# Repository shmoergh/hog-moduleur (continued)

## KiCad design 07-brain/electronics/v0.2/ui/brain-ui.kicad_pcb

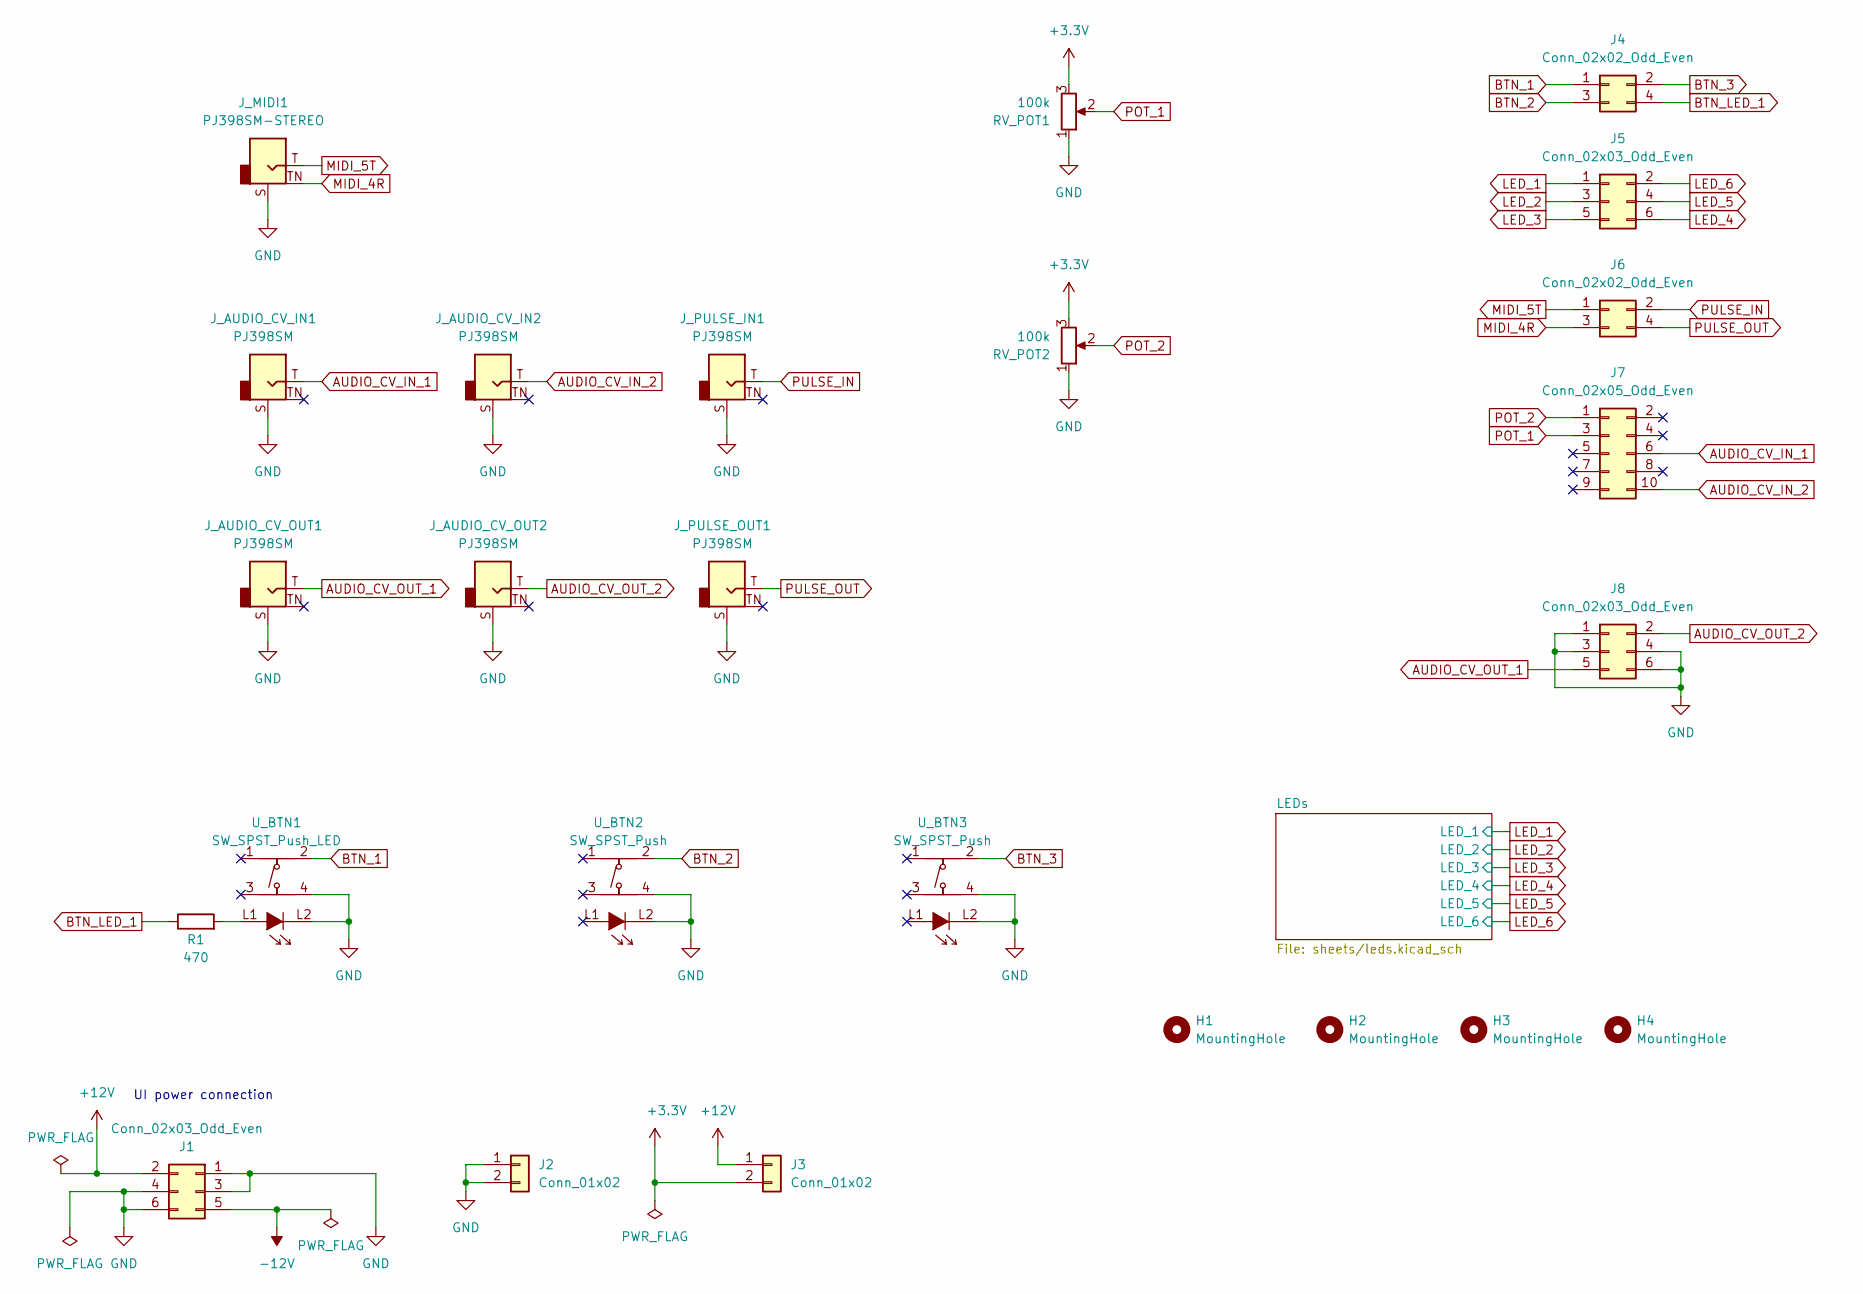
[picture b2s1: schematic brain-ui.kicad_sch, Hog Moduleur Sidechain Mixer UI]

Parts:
H1, H2, H3, H4: MountingHole; MountingHole_3.2mm_M3_DIN965_Pad
J1: Conn_02x03_Odd_Even; PinSocket_2x03_P2.54mm_Vertical; Part no. 200-SSW10301TD
J2: Conn_01x02; PinSocket_1x02_P2.54mm_Vertical; Part no. 200-SSW10201TS
J3: Conn_01x02; PinSocket_1x02_P2.54mm_Vertical
J4, J6: Conn_02x02_Odd_Even; PinSocket_2x02_P2.54mm_Vertical
J5, J8: Conn_02x03_Odd_Even; PinSocket_2x03_P2.54mm_Vertical
J7: Conn_02x05_Odd_Even; PinSocket_2x05_P2.54mm_Vertical
J_AUDIO_CV_IN1, J_AUDIO_CV_IN2: PJ398SM; Jack_3.5mm_QingPu_WQP-PJ398SM_Vertical_CircularHoles; Part no. PJ398SM
J_AUDIO_CV_OUT1, J_AUDIO_CV_OUT2: PJ398SM; Jack_3.5mm_QingPu_WQP-PJ398SM_Vertical_CircularHoles; Part no. PJ398SM
J_MIDI1: PJ398SM-STEREO; Jack_3.5mm_QingPu_WQP-PJ398SM_Vertical_CircularHoles; Part no. PJ398SM
J_PULSE_IN1: PJ398SM; Jack_3.5mm_QingPu_WQP-PJ398SM_Vertical_CircularHoles; Part no. PJ398SM
J_PULSE_OUT1: PJ398SM; Jack_3.5mm_QingPu_WQP-PJ398SM_Vertical_CircularHoles; Part no. PJ398SM
R1: 470; R_Axial_DIN0207_L6.3mm_D2.5mm_P7.62mm_Horizontal
RV_POT1, RV_POT2: 100k; Potentiometer_Bourns_Single-PTV09A; Part no. 652-PTV09A4025FB104
U_BTN1: SW_SPST_Push_LED; SPST_Circular_Pushbutton_LED
U_BTN2, U_BTN3: SW_SPST_Push; SPST_Circular_Pushbutton_LED

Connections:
+3.3V: J3.2, RV_POT1.3, RV_POT2.3
+12V: J1.2, J3.1; also elsewhere on the board
-12V: J1.5
AUDIO_CV_IN_1: J7.6, J_AUDIO_CV_IN1.T
AUDIO_CV_IN_2: J7.10, J_AUDIO_CV_IN2.T
AUDIO_CV_OUT_1: J8.5, J_AUDIO_CV_OUT1.T
AUDIO_CV_OUT_2: J8.2, J_AUDIO_CV_OUT2.T
BTN_1: J4.1, U_BTN1.2
BTN_2: J4.3, U_BTN2.2
BTN_3: J4.2, U_BTN3.2
BTN_LED_1: J4.4, R1.1
GND: J1.1, J1.3, J1.4, J1.6, J2.1, J2.2, J8.1, J8.3, J8.4, J8.6, J_AUDIO_CV_IN1.S, J_AUDIO_CV_IN2.S, J_AUDIO_CV_OUT1.S, J_AUDIO_CV_OUT2.S, J_MIDI1.S, J_PULSE_IN1.S, J_PULSE_OUT1.S, RV_POT1.1, RV_POT2.1, U_BTN1.4, U_BTN1.L2, U_BTN2.4, U_BTN2.L2, U_BTN3.4, U_BTN3.L2; also elsewhere on the board
LED_1: J5.1; also elsewhere on the board
LED_2: J5.3; also elsewhere on the board
LED_3: J5.5; also elsewhere on the board
LED_4: J5.6; also elsewhere on the board
LED_5: J5.4; also elsewhere on the board
LED_6: J5.2; also elsewhere on the board
MIDI_4R: J6.3, J_MIDI1.TN
MIDI_5T: J6.1, J_MIDI1.T
unnamed: R1.2, U_BTN1.L1
POT_1: J7.3, RV_POT1.2
POT_2: J7.1, RV_POT2.2
PULSE_IN: J6.2, J_PULSE_IN1.T
PULSE_OUT: J6.4, J_PULSE_OUT1.T

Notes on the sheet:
UI power connection

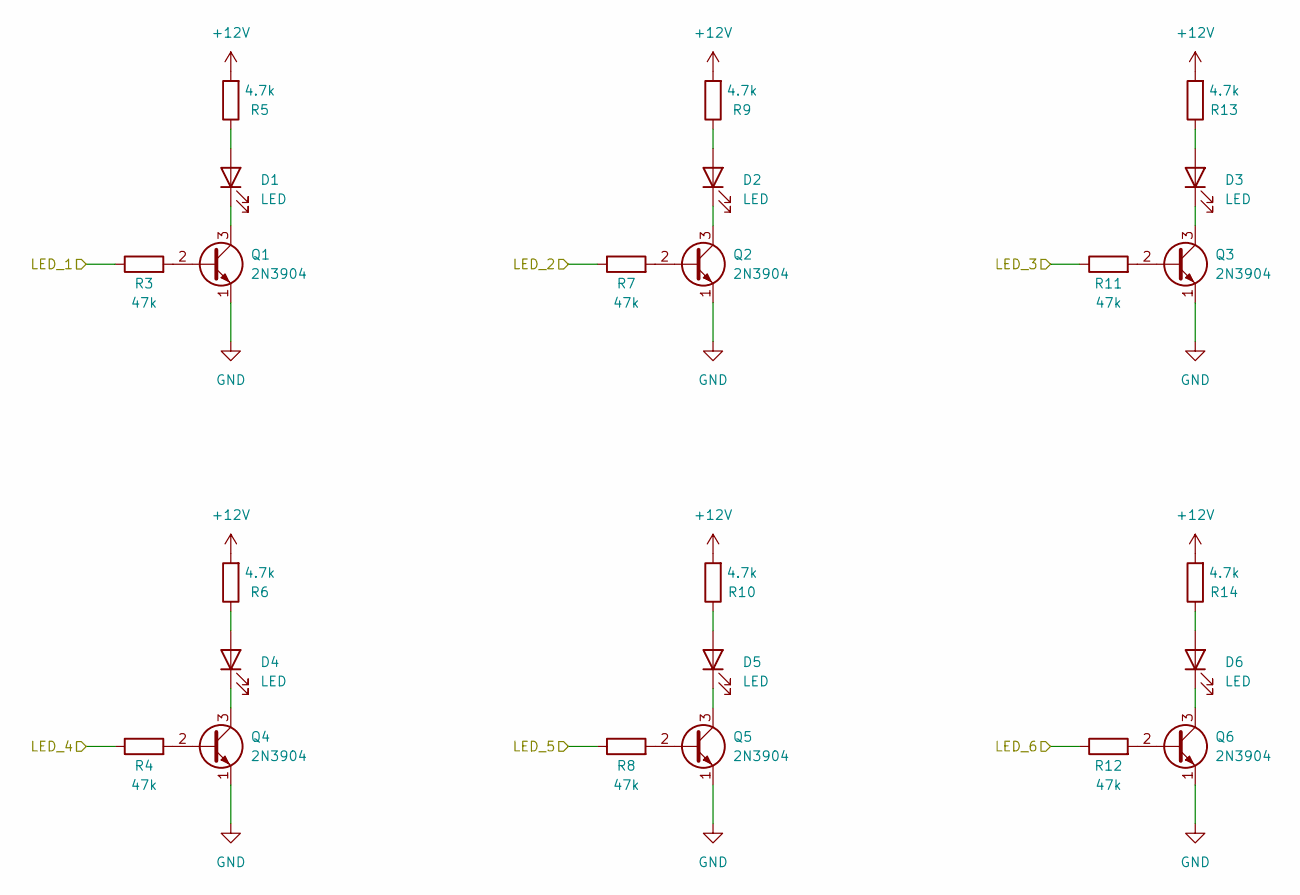
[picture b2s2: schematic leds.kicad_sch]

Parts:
D1, D2, D3, D4, D5, D6: LED; LED_D3.0mm
Q1, Q2, Q3, Q4, Q5, Q6: 2N3904; TO-92_Inline_Wide
R3, R4, R7, R8, R11, R12: 47k; R_Axial_DIN0207_L6.3mm_D2.5mm_P7.62mm_Horizontal; LCSC C25803
R5, R6, R9, R10, R13, R14: 4.7k; R_Axial_DIN0207_L6.3mm_D2.5mm_P7.62mm_Horizontal

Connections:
+12V: R5.2, R6.2, R9.2, R10.2, R13.2, R14.2; also elsewhere on the board
GND: Q1.1 (E), Q2.1 (E), Q3.1 (E), Q4.1 (E), Q5.1 (E), Q6.1 (E); also elsewhere on the board
LED_1: R3.1; also elsewhere on the board
LED_2: R7.1; also elsewhere on the board
LED_3: R11.1; also elsewhere on the board
LED_4: R4.1; also elsewhere on the board
LED_5: R8.1; also elsewhere on the board
LED_6: R12.1; also elsewhere on the board
unnamed: D1.2 (A), R5.1
unnamed: D1.1 (K), Q1.3 (C)
unnamed: D2.2 (A), R9.1
unnamed: D2.1 (K), Q2.3 (C)
unnamed: D3.2 (A), R13.1
unnamed: D3.1 (K), Q3.3 (C)
unnamed: D4.2 (A), R6.1
unnamed: D4.1 (K), Q4.3 (C)
unnamed: D5.2 (A), R10.1
unnamed: D5.1 (K), Q5.3 (C)
unnamed: D6.2 (A), R14.1
unnamed: D6.1 (K), Q6.3 (C)
unnamed: Q1.2 (B), R3.2
unnamed: Q2.2 (B), R7.2
unnamed: Q3.2 (B), R11.2
unnamed: Q4.2 (B), R4.2
unnamed: Q5.2 (B), R8.2
unnamed: Q6.2 (B), R12.2

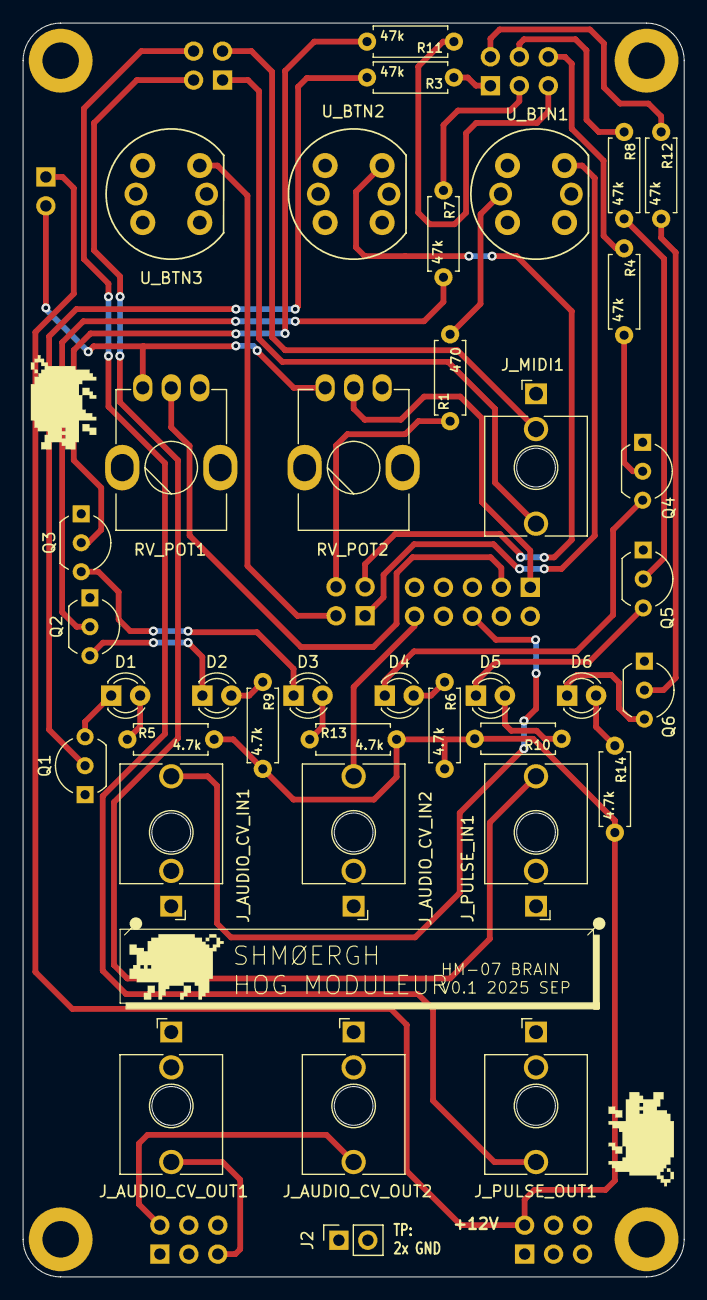
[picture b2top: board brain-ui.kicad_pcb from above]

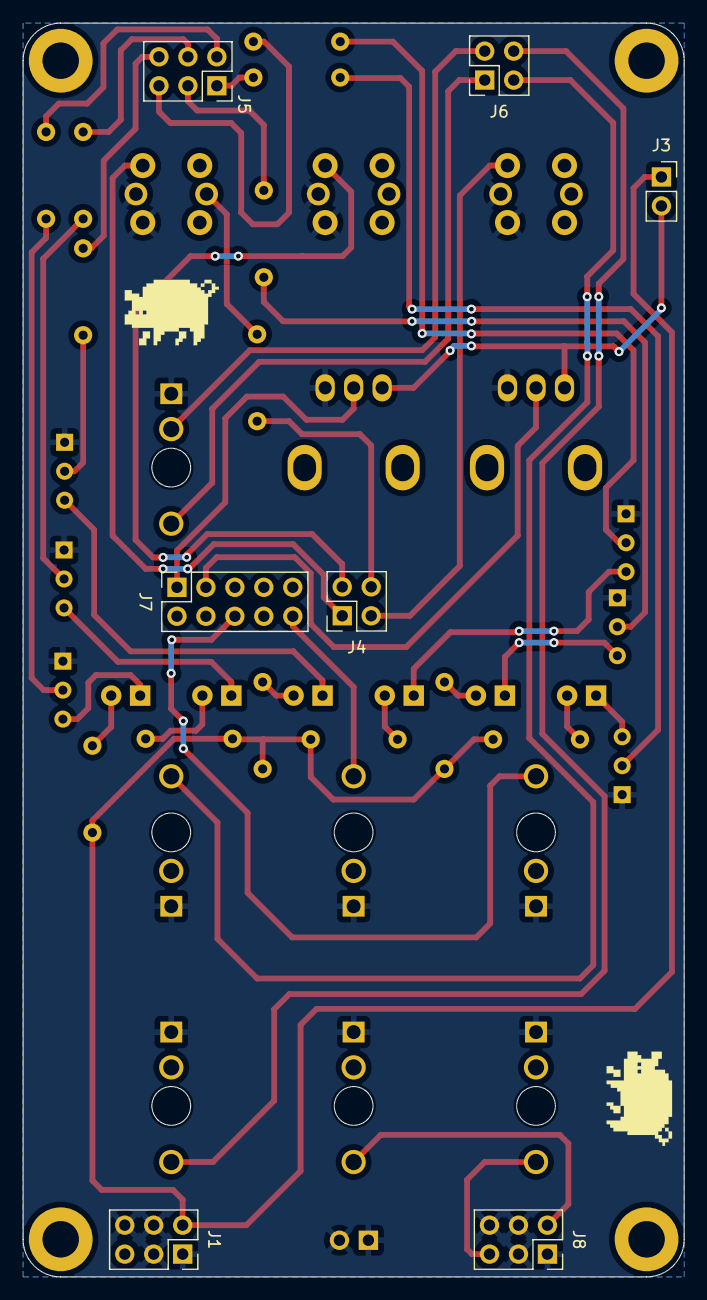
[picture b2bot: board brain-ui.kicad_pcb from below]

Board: 2 copper layers, 58.0 x 110.0 mm, 49 parts (7 on the bottom side), 42 nets.

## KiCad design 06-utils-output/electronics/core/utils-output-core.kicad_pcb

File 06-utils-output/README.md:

# Hog Moduleur / Mods & utils

TBD

## Status

**IN PROGRESS**

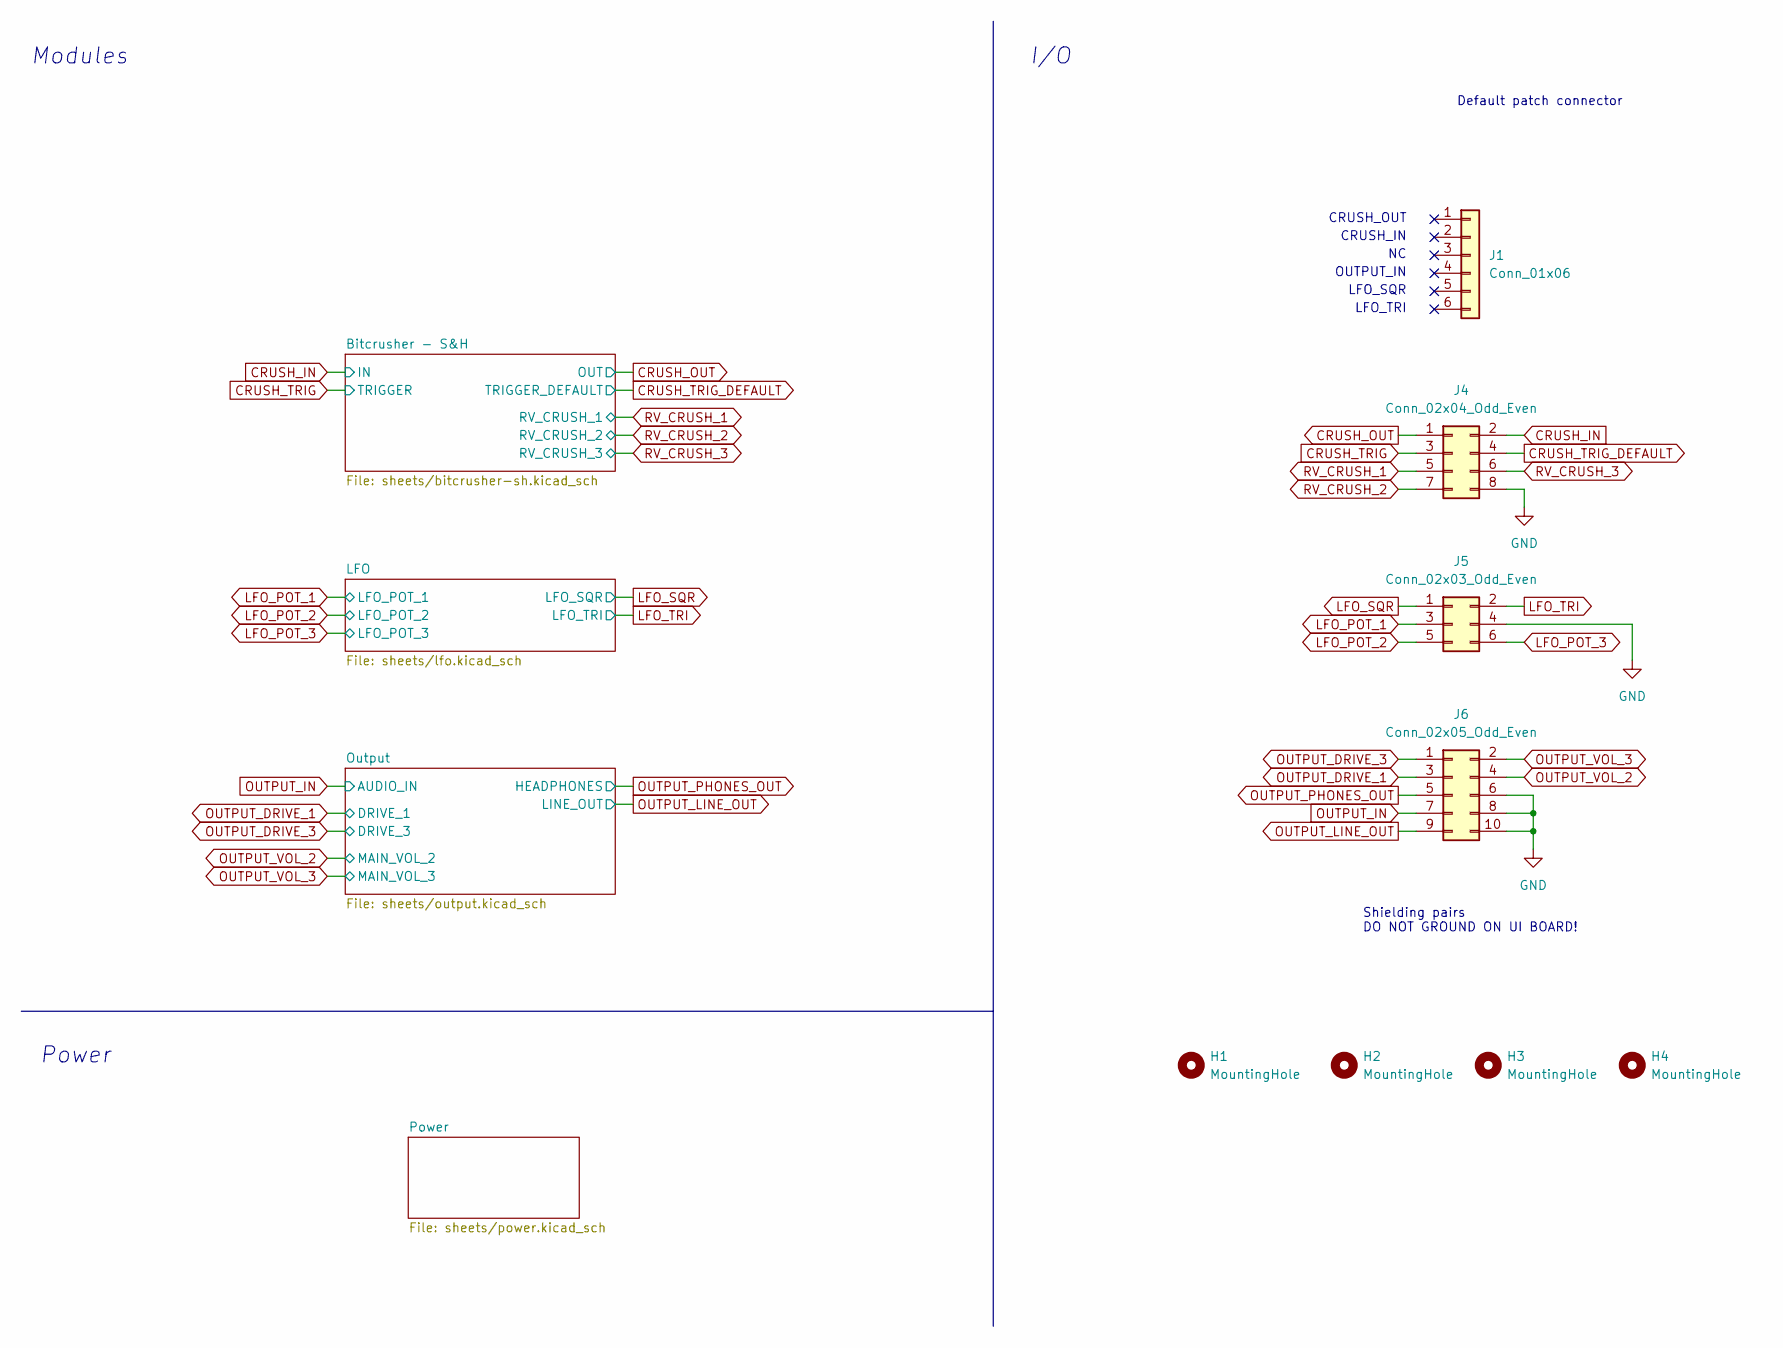
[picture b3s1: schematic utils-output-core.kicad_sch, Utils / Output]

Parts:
H1, H2, H3, H4: MountingHole; MountingHole_3.2mm_M3_DIN965_Pad
J1: Conn_01x06; PinHeader_1x06_P2.54mm_Vertical
J4: Conn_02x04_Odd_Even; PinHeader_2x04_P2.54mm_Vertical
J5: Conn_02x03_Odd_Even; PinHeader_2x03_P2.54mm_Vertical
J6: Conn_02x05_Odd_Even; PinHeader_2x05_P2.54mm_Vertical

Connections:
CRUSH_IN: J4.2; also elsewhere on the board
CRUSH_OUT: J4.1; also elsewhere on the board
CRUSH_TRIG: J4.3; also elsewhere on the board
CRUSH_TRIG_DEFAULT: J4.4; also elsewhere on the board
GND: J4.8, J5.4, J6.6, J6.8, J6.10; also elsewhere on the board
LFO_POT_1: J5.3; also elsewhere on the board
LFO_POT_2: J5.5; also elsewhere on the board
LFO_POT_3: J5.6; also elsewhere on the board
LFO_SQR: J5.1; also elsewhere on the board
LFO_TRI: J5.2; also elsewhere on the board
OUTPUT_DRIVE_1: J6.3; also elsewhere on the board
OUTPUT_DRIVE_3: J6.1; also elsewhere on the board
OUTPUT_IN: J6.7; also elsewhere on the board
OUTPUT_LINE_OUT: J6.9; also elsewhere on the board
OUTPUT_PHONES_OUT: J6.5; also elsewhere on the board
OUTPUT_VOL_2: J6.4; also elsewhere on the board
OUTPUT_VOL_3: J6.2; also elsewhere on the board
RV_CRUSH_1: J4.5; also elsewhere on the board
RV_CRUSH_2: J4.7; also elsewhere on the board
RV_CRUSH_3: J4.6; also elsewhere on the board

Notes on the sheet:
Power
LFO_TRI
CRUSH_OUT
Shielding pairs DO NOT GROUND ON UI BOARD!
Default patch connector
LFO_SQR
Modules
CRUSH_IN
I/O
OUTPUT_IN

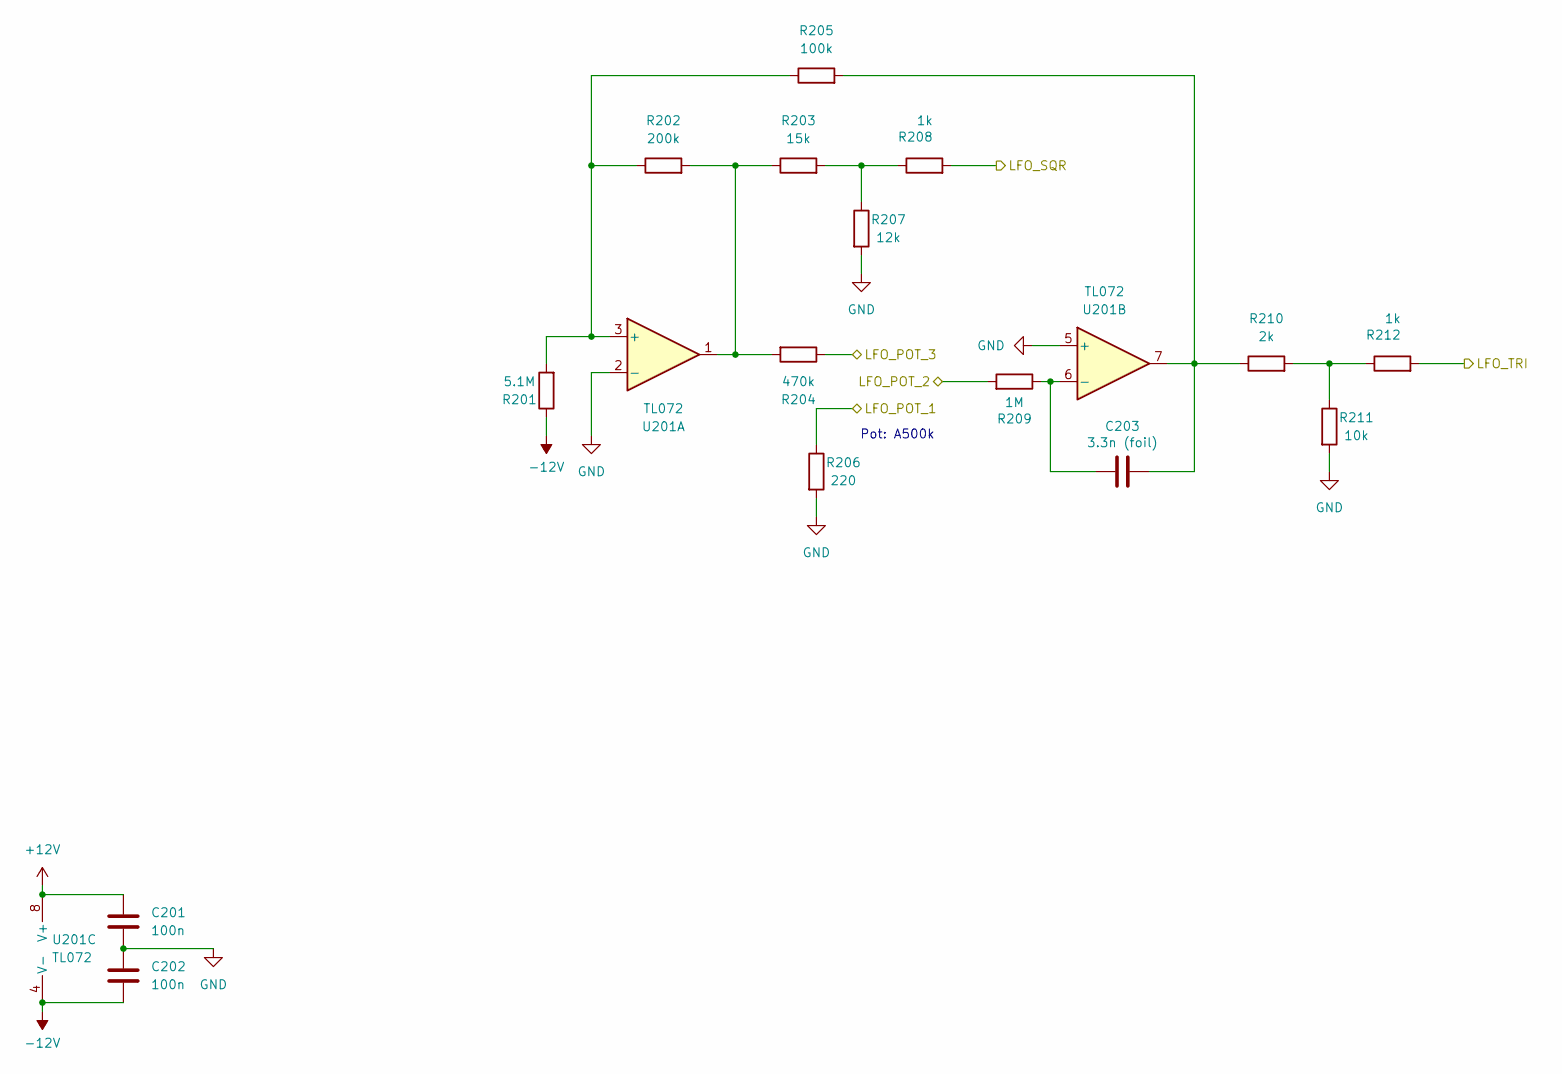
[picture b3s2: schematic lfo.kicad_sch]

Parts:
C201, C202: 100n; C_0603_1608Metric; LCSC C14663
C203: 3.3n (foil); C_Rect_L7.0mm_W2.5mm_P5.00mm; Part No. 80-R82EC1330AA50K
R201: 5.1M; R_0603_1608Metric; LCSC C13320
R202: 200k; R_0603_1608Metric; LCSC C25811
R203: 15k; R_0603_1608Metric; LCSC C25811
R204: 470k; R_0603_1608Metric; LCSC C23178
R205: 100k; R_0603_1608Metric; LCSC C25803
R206: 220; R_Axial_DIN0207_L6.3mm_D2.5mm_P7.62mm_Horizontal
R207: 12k; R_0603_1608Metric; LCSC C22962
R208, R212: 1k; R_0603_1608Metric; LCSC C21190
R209: 1M; R_0603_1608Metric; LCSC C22935
R210: 2k; R_0603_1608Metric; LCSC C25811
R211: 10k; R_0603_1608Metric; LCSC C22962
U201: TL072; SOIC-8_3.9x4.9mm_P1.27mm; LCSC C6961

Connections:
GND: C201.2, C202.1, R206.2, R207.2, R211.2, U201.2 (-), U201.5 (+); also elsewhere on the board
LFO_POT_1: R206.1; also elsewhere on the board
LFO_POT_2: R209.2; also elsewhere on the board
LFO_POT_3: R204.1; also elsewhere on the board
LFO_SQR: R208.2; also elsewhere on the board
LFO_TRI: R212.2; also elsewhere on the board
unnamed: C203.1, R205.2, R210.1, U201.7
unnamed: R202.2, R203.1, R204.2, U201.1
unnamed: R203.2, R207.1, R208.1
unnamed: R210.2, R211.1, R212.1
unnamed: R201.2, R202.1, R205.1, U201.3 (+)
unnamed: C203.2, R209.1, U201.6 (-)

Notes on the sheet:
Pot: A500k

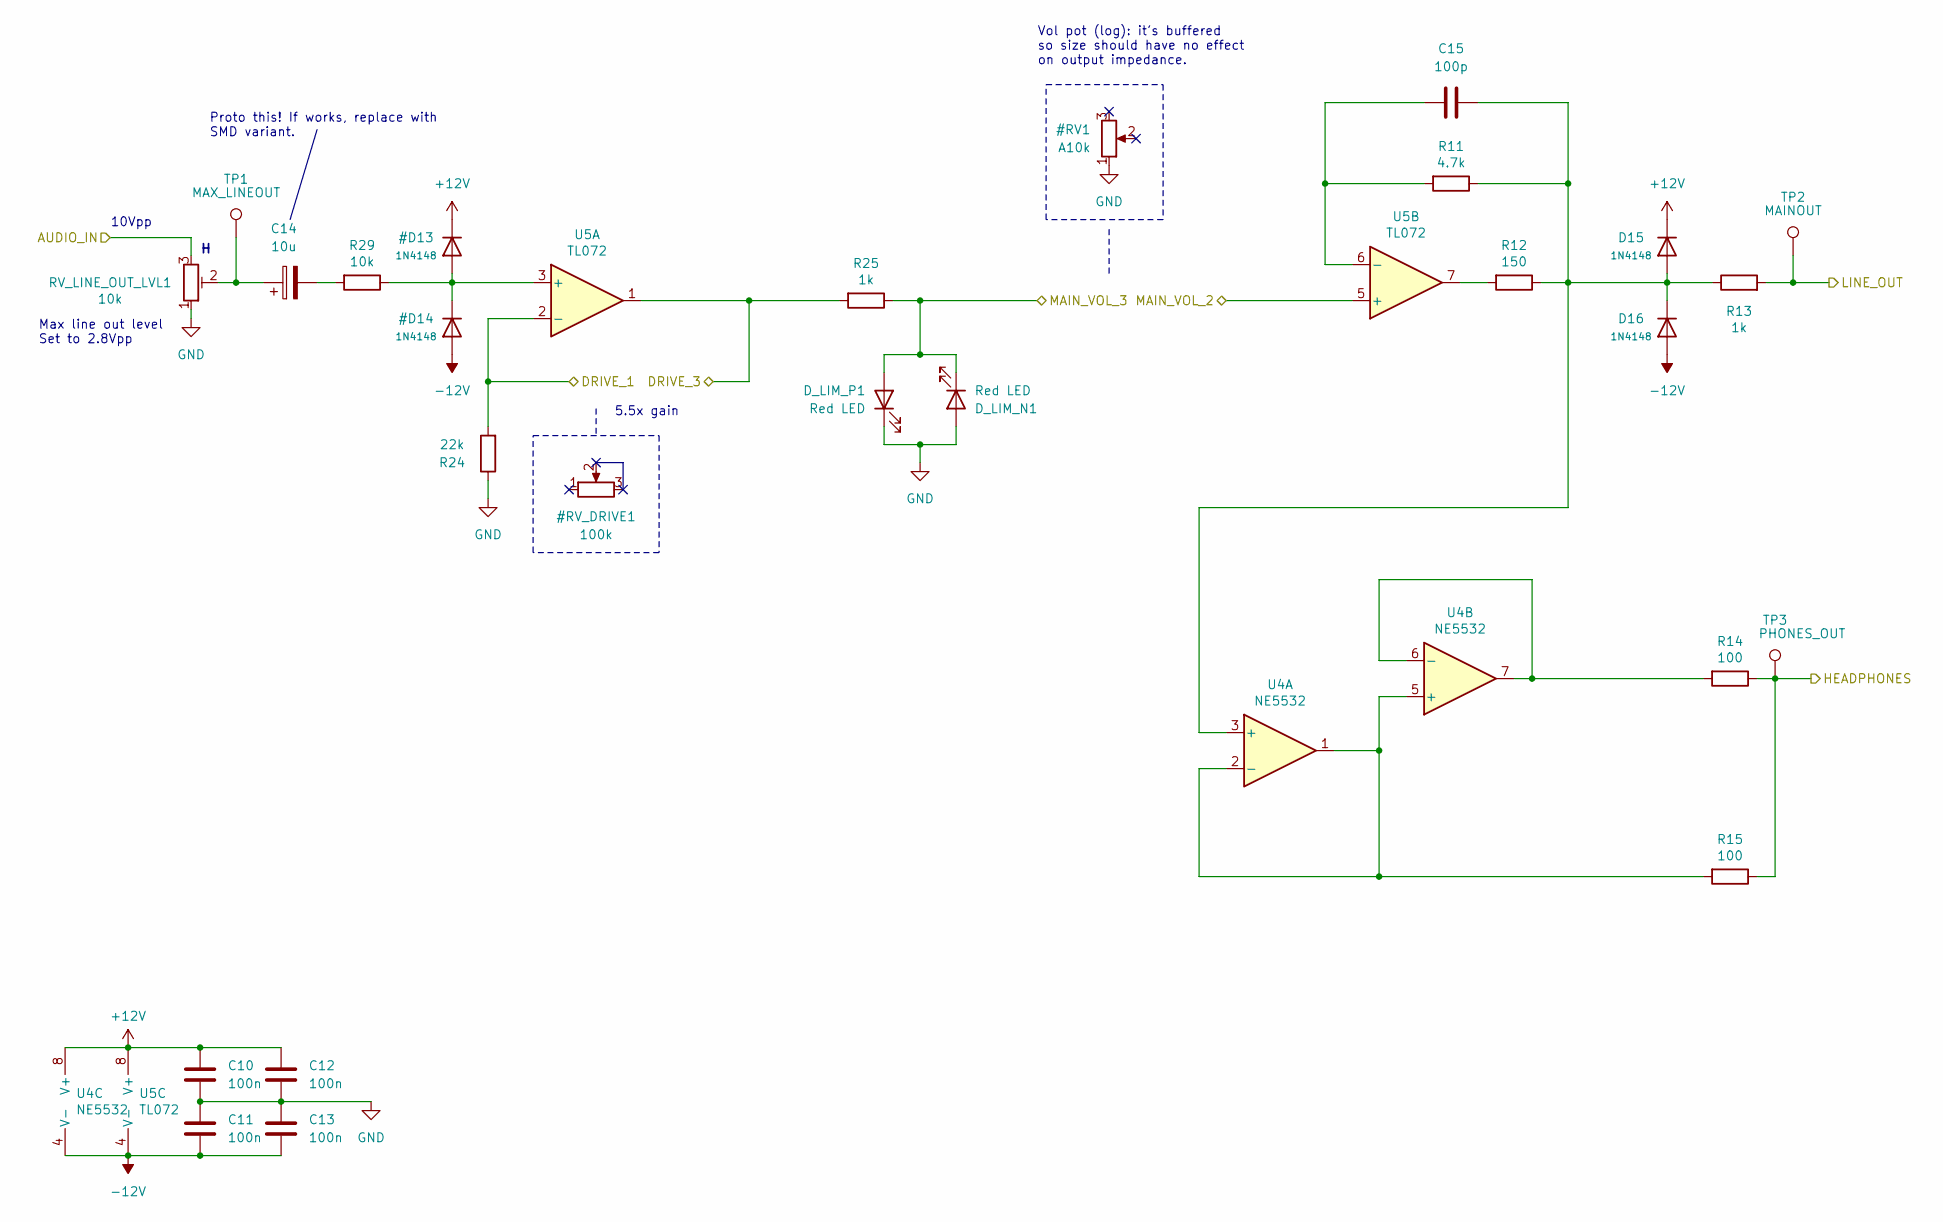
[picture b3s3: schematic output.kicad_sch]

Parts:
C10, C11, C12, C13: 100n; C_0603_1608Metric; LCSC C14663
C14: 10u; CP_Elec_5x5.4; LCSC C4747971
C15: 100p; C_0603_1608Metric; LCSC C14858
D15, D16: 1N4148; D_SOD-123; LCSC C81598
D_LIM_N1: Red LED; LED_D3.0mm
D_LIM_P1: Red LED; LED_D5.0mm
R11: 4.7k; R_0603_1608Metric; LCSC C23162
R12: 150; R_0603_1608Metric; LCSC C22808
R13, R25: 1k; R_0603_1608Metric; LCSC C21190
R14, R15: 100; R_0603_1608Metric; LCSC C22775
R24: 22k; R_0603_1608Metric; LCSC C31850
R29: 10k; R_0603_1608Metric; LCSC C25804
RV_LINE_OUT_LVL1: 10k; Potentiometer_ACP_CA6-H2,5_Horizontal; Part No. 531-PT6KH-10K
TP1: MAX_LINEOUT; TestPoint_THTPad_D1.5mm_Drill0.7mm
TP2: MAINOUT; TestPoint_THTPad_2.0x2.0mm_Drill1.0mm
TP3: PHONES_OUT; TestPoint_THTPad_2.0x2.0mm_Drill1.0mm
U4: NE5532; SOIC-8_3.9x4.9mm_P1.27mm; LCSC C7426
U5: TL072; SOIC-8_3.9x4.9mm_P1.27mm; LCSC C6961

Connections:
GND: C10.2, C11.1, C12.2, C13.1, D_LIM_N1.2 (A), D_LIM_P1.1 (K), R24.1, RV_LINE_OUT_LVL1.1; also elsewhere on the board
unnamed: C14.1, RV_LINE_OUT_LVL1.2, TP1.1
unnamed: C14.2, R29.2
unnamed: C15.2, D15.2 (A), D16.1 (K), R11.1, R12.1, R13.1, U4.3 (+)
unnamed: R12.2, U5.7
unnamed: R15.2, U4.1, U4.2 (-), U4.5 (+)
unnamed: R14.2, U4.6 (-), U4.7
unnamed: C15.1, R11.2, U5.6 (-)
OUTPUT_DRIVE_1: R24.2, U5.2 (-); also elsewhere on the board
OUTPUT_DRIVE_3: R25.2, U5.1; also elsewhere on the board
OUTPUT_IN: RV_LINE_OUT_LVL1.3; also elsewhere on the board
OUTPUT_LINE_OUT: R13.2, TP2.1; also elsewhere on the board
OUTPUT_PHONES_OUT: R14.1, R15.1, TP3.1; also elsewhere on the board
OUTPUT_VOL_2: U5.5 (+); also elsewhere on the board
OUTPUT_VOL_3: D_LIM_N1.1 (K), D_LIM_P1.2 (A), R25.1; also elsewhere on the board

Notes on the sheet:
Vol pot (log): it's buffered so size should have no effect on output impedance.
5.5x gain
Proto this! If works, replace with SMD variant.
Max line out level Set to 2.8Vpp
10Vpp

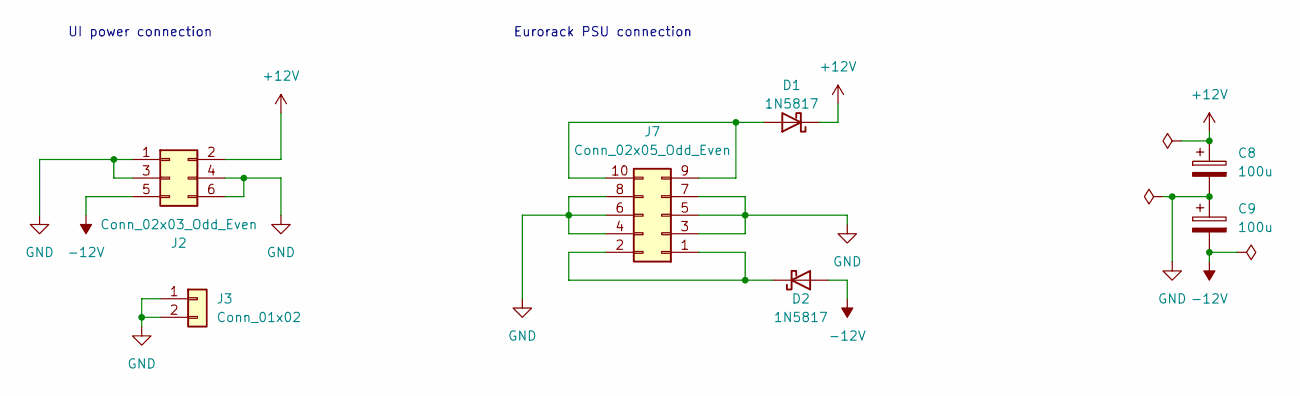
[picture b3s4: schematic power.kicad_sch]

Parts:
C8, C9: 100u; CP_Elec_6.3x7.7; LCSC C2836437
D1, D2: 1N5817; D_SOD-323; LCSC C5190152
J2: Conn_02x03_Odd_Even; PinHeader_2x03_P2.54mm_Vertical
J3: Conn_01x02; PinHeader_1x02_P2.54mm_Vertical
J7: Conn_02x05_Odd_Even; IDC-Header_2x05_P2.54mm_Horizontal

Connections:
GND: C8.2, C9.1, J2.1, J2.3, J2.4, J2.6, J3.1, J3.2, J7.3, J7.4, J7.5, J7.6, J7.7, J7.8; also elsewhere on the board
unnamed: D1.2 (A), J7.9, J7.10
unnamed: D2.1 (K), J7.1, J7.2

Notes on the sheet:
UI power connection
Eurorack PSU connection

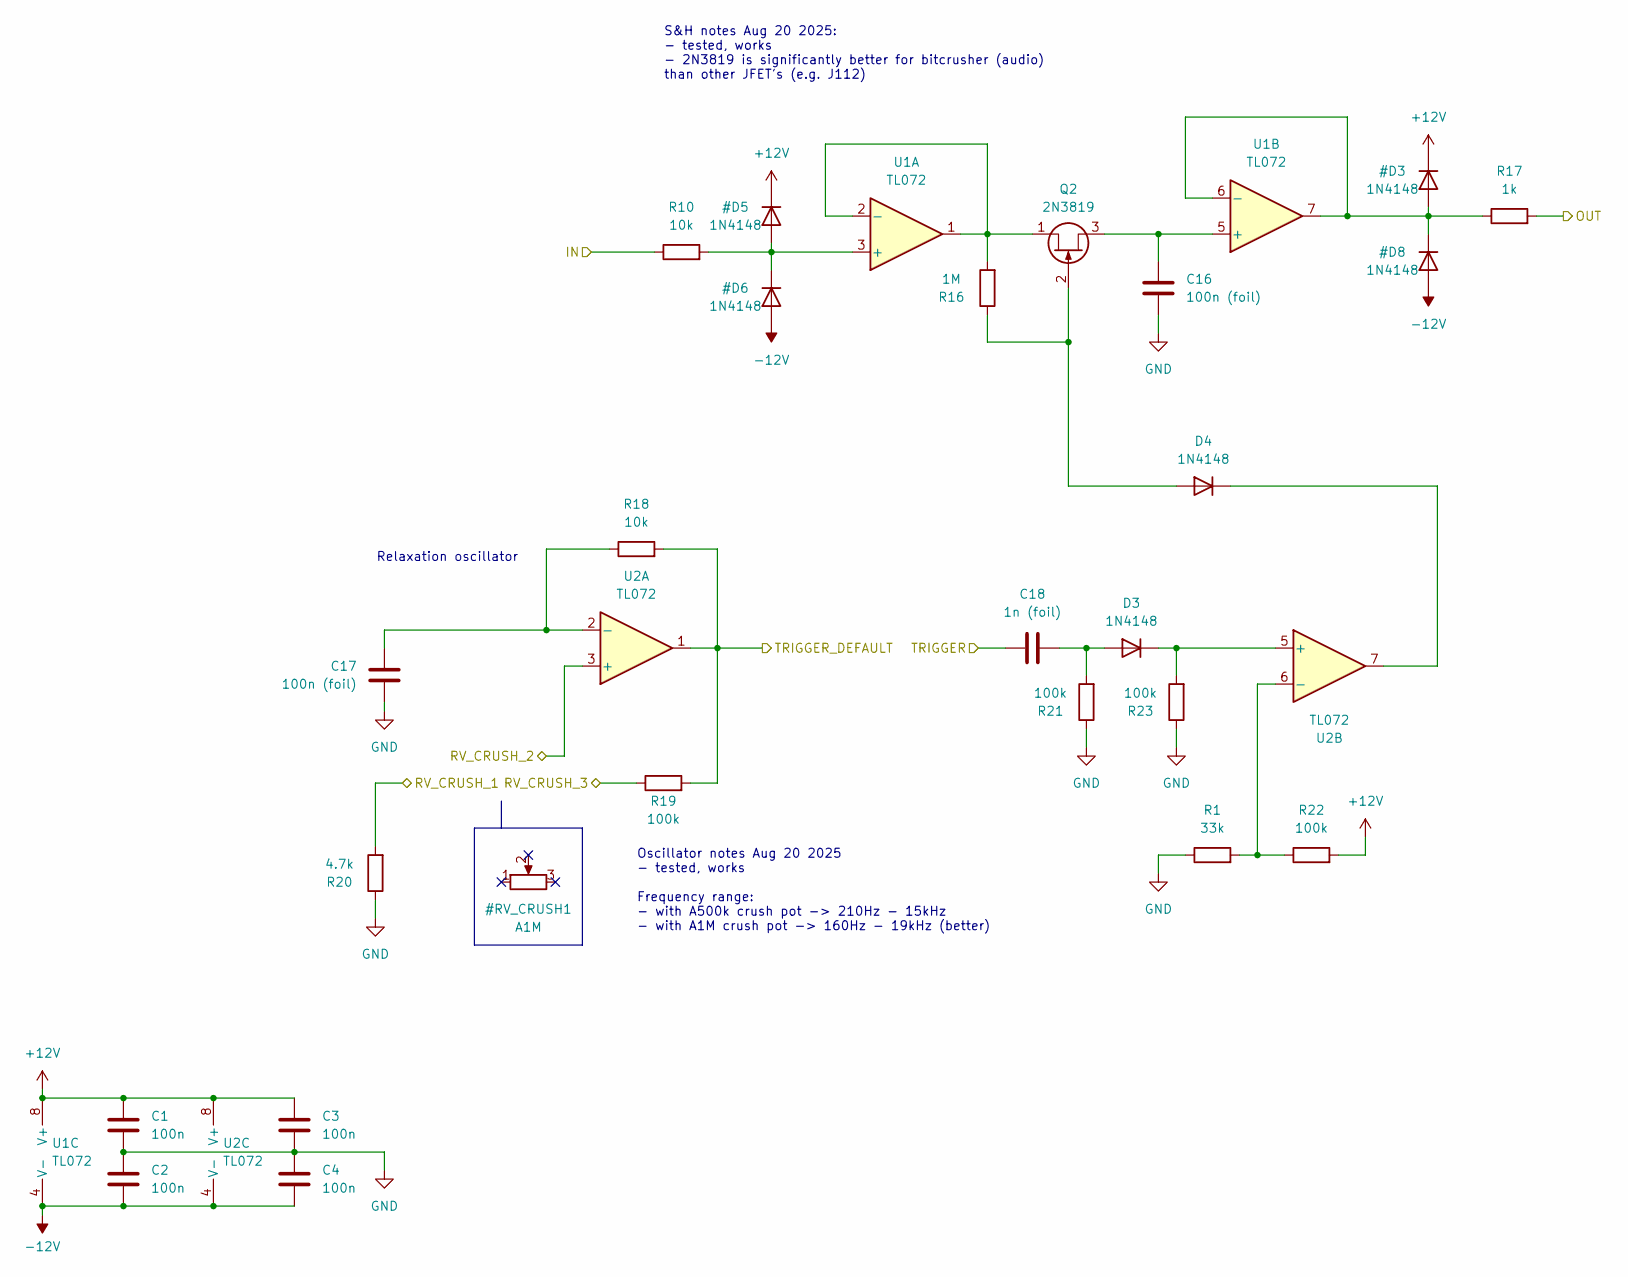
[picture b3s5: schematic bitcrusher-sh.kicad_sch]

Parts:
C1, C2, C3, C4: 100n; C_0603_1608Metric; LCSC C14663
C16, C17: 100n (foil); C_Rect_L7.2mm_W2.5mm_P5.00mm_FKS2_FKP2_MKS2_MKP2
C18: 1n (foil); C_Rect_L7.2mm_W2.5mm_P5.00mm_FKS2_FKP2_MKS2_MKP2
D3, D4: 1N4148; D_SOD-123; LCSC C81598
Q2: 2N3819; TO-92_Inline_Wide
R1: 33k; R_0603_1608Metric; LCSC C4216
R10, R18: 10k; R_0603_1608Metric; LCSC C25804
R16: 1M; R_0603_1608Metric; LCSC C22935
R17: 1k; R_0603_1608Metric; LCSC C21190
R19, R21, R22, R23: 100k; R_0603_1608Metric; LCSC C25803
R20: 4.7k; R_0603_1608Metric; LCSC C23162
U1, U2: TL072; SOIC-8_3.9x4.9mm_P1.27mm; LCSC C6961

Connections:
CRUSH_IN: R10.1; also elsewhere on the board
CRUSH_OUT: R17.2; also elsewhere on the board
CRUSH_TRIG: C18.1; also elsewhere on the board
CRUSH_TRIG_DEFAULT: R18.2, R19.2, U2.1; also elsewhere on the board
GND: C1.2, C2.1, C3.2, C4.1, C16.2, C17.2, R1.1, R20.1, R21.1, R23.1; also elsewhere on the board
unnamed: C18.2, D3.2 (A), R21.2
unnamed: D3.1 (K), R23.2, U2.5 (+)
unnamed: D4.2 (A), Q2.2 (G), R16.1
unnamed: D4.1 (K), U2.7
unnamed: Q2.1 (D), R16.2, U1.1, U1.2 (-)
unnamed: C16.1, Q2.3 (S), U1.5 (+)
unnamed: C17.1, R18.1, U2.2 (-)
unnamed: R1.2, R22.1, U2.6 (-)
RV_CRUSH_1: R20.2; also elsewhere on the board
RV_CRUSH_2: U2.3 (+); also elsewhere on the board
RV_CRUSH_3: R19.1; also elsewhere on the board

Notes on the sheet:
Relaxation oscillator
S&H notes Aug 20 2025: - tested, works - 2N3819 is significantly better for bitcrusher (audio) than other JFET's (e.g. J112)
Oscillator notes Aug 20 2025 - tested, works Frequency range: - with A500k crush pot -> 210Hz - 15kHz - with A1M crush pot -> 160Hz - 19kHz (better)

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
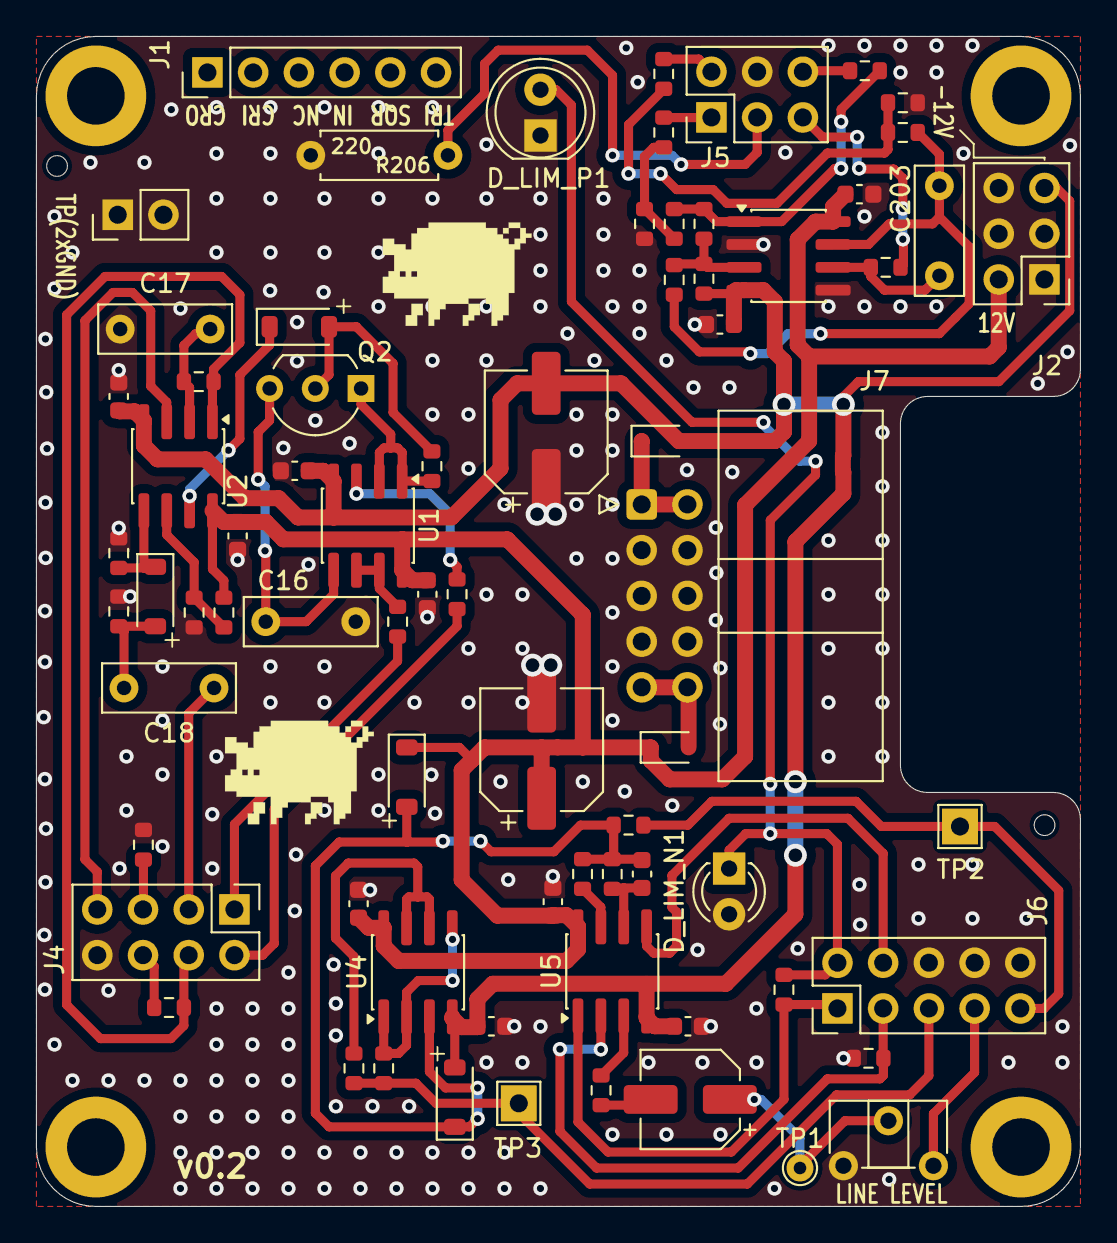
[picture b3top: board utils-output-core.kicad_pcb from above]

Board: 2 copper layers, 58.0 x 65.0 mm, 77 parts (0 on the bottom side), 48 nets.
